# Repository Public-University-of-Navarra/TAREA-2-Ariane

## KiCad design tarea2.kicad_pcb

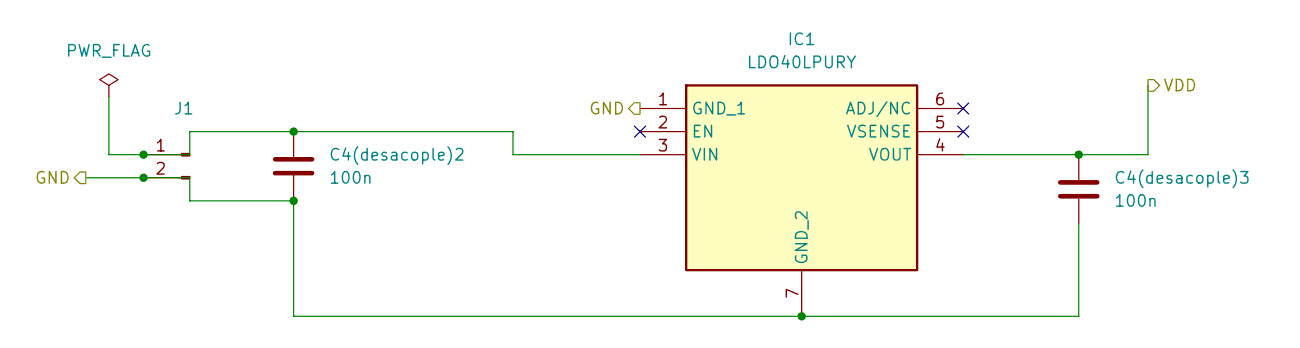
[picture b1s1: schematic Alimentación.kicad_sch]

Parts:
C4(desacople)2, C4(desacople)3: 100n; C_0805_2012Metric
IC1: LDO40LPURY; DFN-6-1EP_3x3mm_P0.95mm_EP1.7x2.6mm; Manufacturer_Part_Number LDO40LPURY; Mouser Part Number 511-LDO40LPURY
J1: Conn_01x02_Pin; PinHeader_1x02_P1.00mm_Horizontal

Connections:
/Alimentación/GND: C4(desacople)2.2, C4(desacople)3.2, IC1.1 (GND_1), IC1.7 (GND_2), J1.2; also elsewhere on the board
/Alimentación/VDD: C4(desacople)3.1, IC1.4 (VOUT); also elsewhere on the board
unnamed: C4(desacople)2.1, IC1.3 (VIN), J1.1

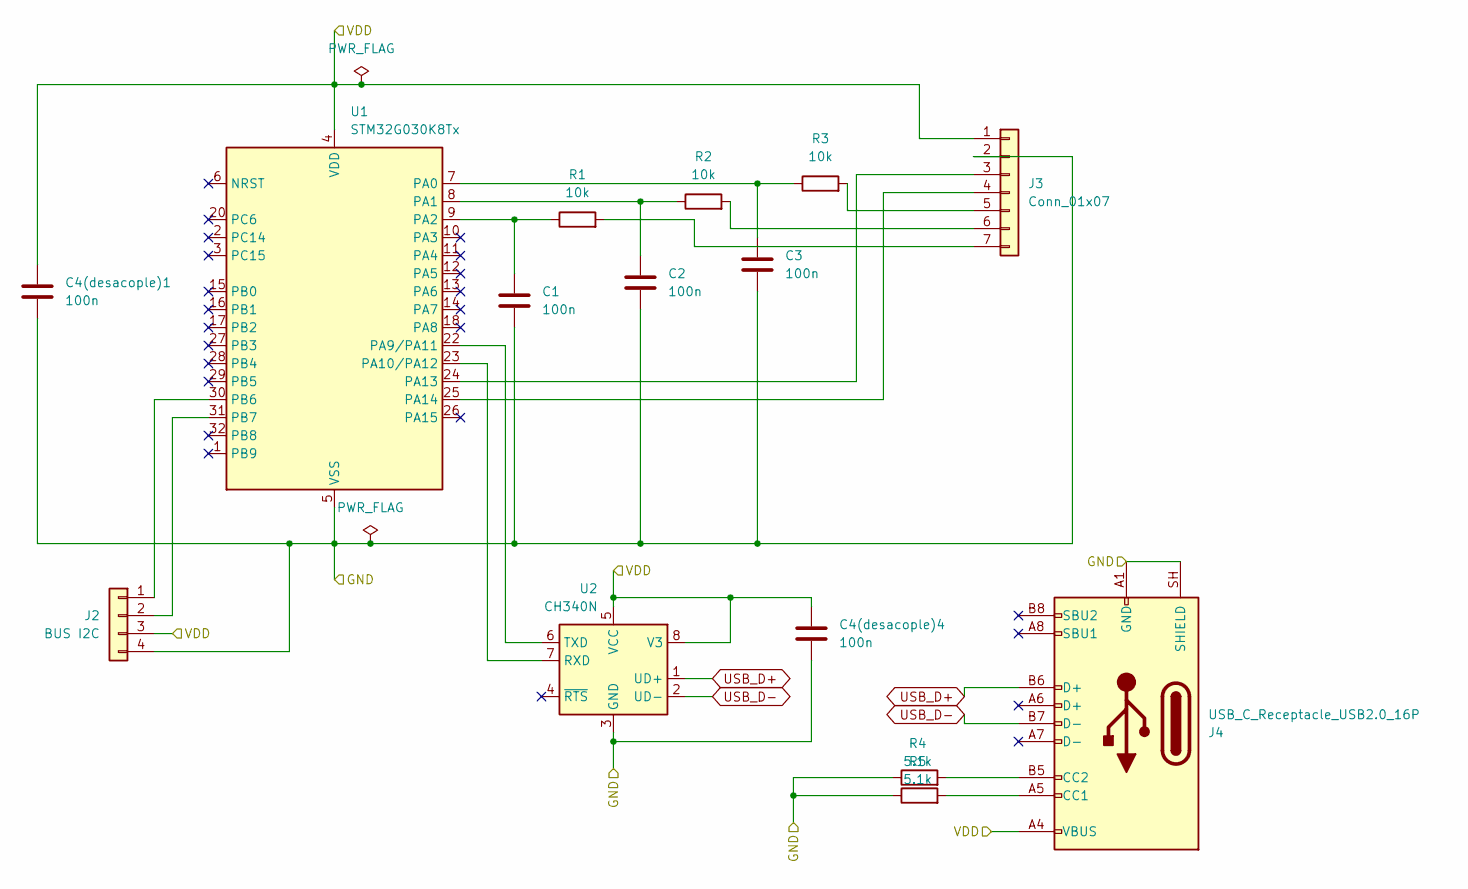
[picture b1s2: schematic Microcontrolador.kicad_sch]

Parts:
C1, C2, C3, C4(desacople)1, C4(desacople)4: 100n; C_0805_2012Metric
J2: BUS I2C; PinHeader_1x04_P2.54mm_Vertical
J3: Conn_01x07; PinHeader_1x07_P2.54mm_Horizontal
J4: USB_C_Receptacle_USB2.0_16P; USB_C_Receptacle_GCT_USB4105-xx-A_16P_TopMnt_Horizontal
R1, R2, R3: 10k; R_0805_2012Metric
R4, R5: 5.1k; R_0805_2012Metric
U1: STM32G030K8Tx; LQFP-32_7x7mm_P0.8mm
U2: CH340N; JEITA_SOIC-8_3.9x4.9mm_P1.27mm

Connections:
/Alimentación/GND: C1.2, C2.2, C3.2, C4(desacople)1.2, C4(desacople)4.2, J2.4, J3.2, J4.A1 (GND), J4.A12 (GND), J4.B1 (GND), J4.B12 (GND), J4.SH (SHIELD), R4.1, R5.1, U1.5 (VSS), U2.3 (GND); also elsewhere on the board
/Alimentación/VDD: C4(desacople)1.1, C4(desacople)4.1, J2.3, J3.1, J4.A4 (VBUS), J4.A9 (VBUS), J4.B4 (VBUS), J4.B9 (VBUS), U1.4 (VDD), U2.5 (VCC), U2.8 (V3); also elsewhere on the board
unnamed: J2.1, U1.30 (PB6)
unnamed: J2.2, U1.31 (PB7)
unnamed: J3.3, U1.24 (PA13)
unnamed: J3.4, U1.25 (PA14)
unnamed: J3.5, R3.2
unnamed: J3.6, R2.2
unnamed: J3.7, R1.2
unnamed: J4.A5 (CC1), R5.2
unnamed: J4.B5 (CC2), R4.2
unnamed: C3.1, R3.1, U1.7 (PA0)
unnamed: C2.1, R2.1, U1.8 (PA1)
unnamed: C1.1, R1.1, U1.9 (PA2)
unnamed: U1.22 (PA9/PA11), U2.6 (TXD)
unnamed: U1.23 (PA10/PA12), U2.7 (RXD)
USB_D+: J4.B6 (D+), U2.1 (UD+)
USB_D-: J4.B7 (D-), U2.2 (UD-)

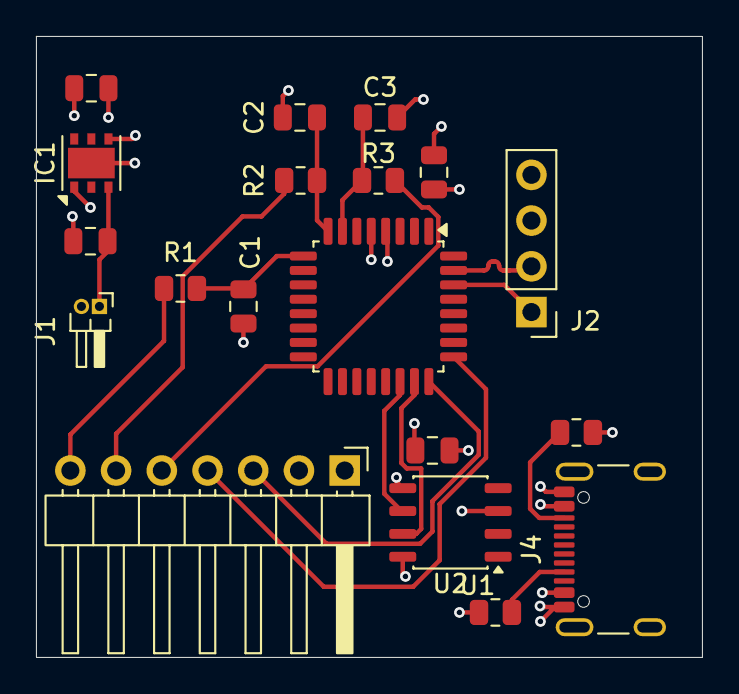
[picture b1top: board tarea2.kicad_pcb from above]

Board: 4 copper layers, 37.0 x 34.5 mm, 19 parts (0 on the bottom side), 19 nets.
